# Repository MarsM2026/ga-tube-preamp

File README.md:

# Warm opamp preamp – tube character, designed by a genetic algorithm

A stereo hi-fi preamp built with opamps that imitates the warm distortion character
of a **12AX7 tube stage**. The component values were found by a **genetic
algorithm** that compared thousands of ngspice simulations against a simulated tube.
Includes the KiCad 10 schematic, two PCB designs (through-hole to solder yourself,
SMD to have it assembled by a PCB fab) and full documentation.

A project by **KyntoSoftware**.

| | |
|---|---|
| Gain | 10 dB |
| Frequency response | 20 Hz – 20 kHz ±0.11 dB |
| Distortion at 1 V rms | 0.31 % (almost only H2, the same as the 12AX7) |
| Signal-to-noise | approx. 97.5 dB re 1 V rms |
| Parts | 3× NE5532, 12× 1N4148, 1 % resistors, 2 trimmers |
| Power | ±15 V regulated |
| PCB | 2 layers; through-hole 178 × 100 mm or SMD 129 × 72 mm (assembled by a fab) |

**Status:** fully simulated and checked (NE5532 model, Monte Carlo tolerances,
ERC/DRC without errors). Not yet physically built and measured.

## Where to find what

| Folder / file | Content |
|---|---|
| [docs/](docs/README.md) | **documentation**: how it works, design process, results, build guide |
| `docs/img/`, `docs/data/` | charts and raw numbers (JSON/CSV) |
| `hardware/kicad/`, `hardware/export/` | through-hole: KiCad 10 project, Gerbers, schematic PDF/SVG, PCB layers, 3D renders, parts list |
| `hardware/kicad_smd/`, `hardware/export_smd/` | SMD version: same, plus assembly files for the fab ([explanation](docs/07_assembled_smd.md)) |
| `designs/` | design values per GA run and the final design (`final.json`) |
| `circuitbuilder/` | Python package: ngspice wrapper, analysis, candidate, fitness, as-built design |
| `scripts/` | every step: reference, GA, checks, schematic, PCB, documentation |

## Quick start

```powershell
python -m venv .venv
.\.venv\Scripts\pip install -r requirements.txt
.\.venv\Scripts\python scripts\verify_build.py      # simulate the as-built circuit
.\.venv\Scripts\python scripts\make_hardware.py     # KiCad schematic, PCB, Gerbers, renders
.\.venv\Scripts\python scripts\make_hardware.py --variant smd   # same for the SMD version
```

Requires ngspice 47 in `tools/Spice64`, KiCad 10, and Java + Freerouting 2.5 in
`tools/freerouting/`. See [docs/06_software.md](docs/06_software.md) for all steps.

## License

Copyright © 2026 KyntoSoftware. Each kind of work has the license that was made for it.
All three are permissive: you may use, modify, share and sell, also commercially, as
long as you credit KyntoSoftware.

| What | License | File |
|---|---|---|
| Software (`circuitbuilder/`, `scripts/`) | MIT | [LICENSE](LICENSE) |
| Hardware design (`hardware/`, `designs/`) | CERN-OHL-P v2 | [LICENSE-HARDWARE](LICENSE-HARDWARE) |
| Documentation, charts and images (`docs/`) | CC BY 4.0 | [LICENSE-DOCS](LICENSE-DOCS) |

Third-party simulation models keep their own terms: the NE5534 macromodel in
`circuitbuilder/models/ne5532.lib` (TI/MicroSim, via the
[KiCad-Spice-Library](https://github.com/kicad-spice-library/KiCad-Spice-Library)) and
the 12AX7 model in `circuitbuilder/models/12ax7.lib` (after Norman Koren).

The design is provided as is, without warranty; see the license files. Building it
involves a ±15 V supply; mains-powered supplies should only be built by people
experienced with mains voltage.

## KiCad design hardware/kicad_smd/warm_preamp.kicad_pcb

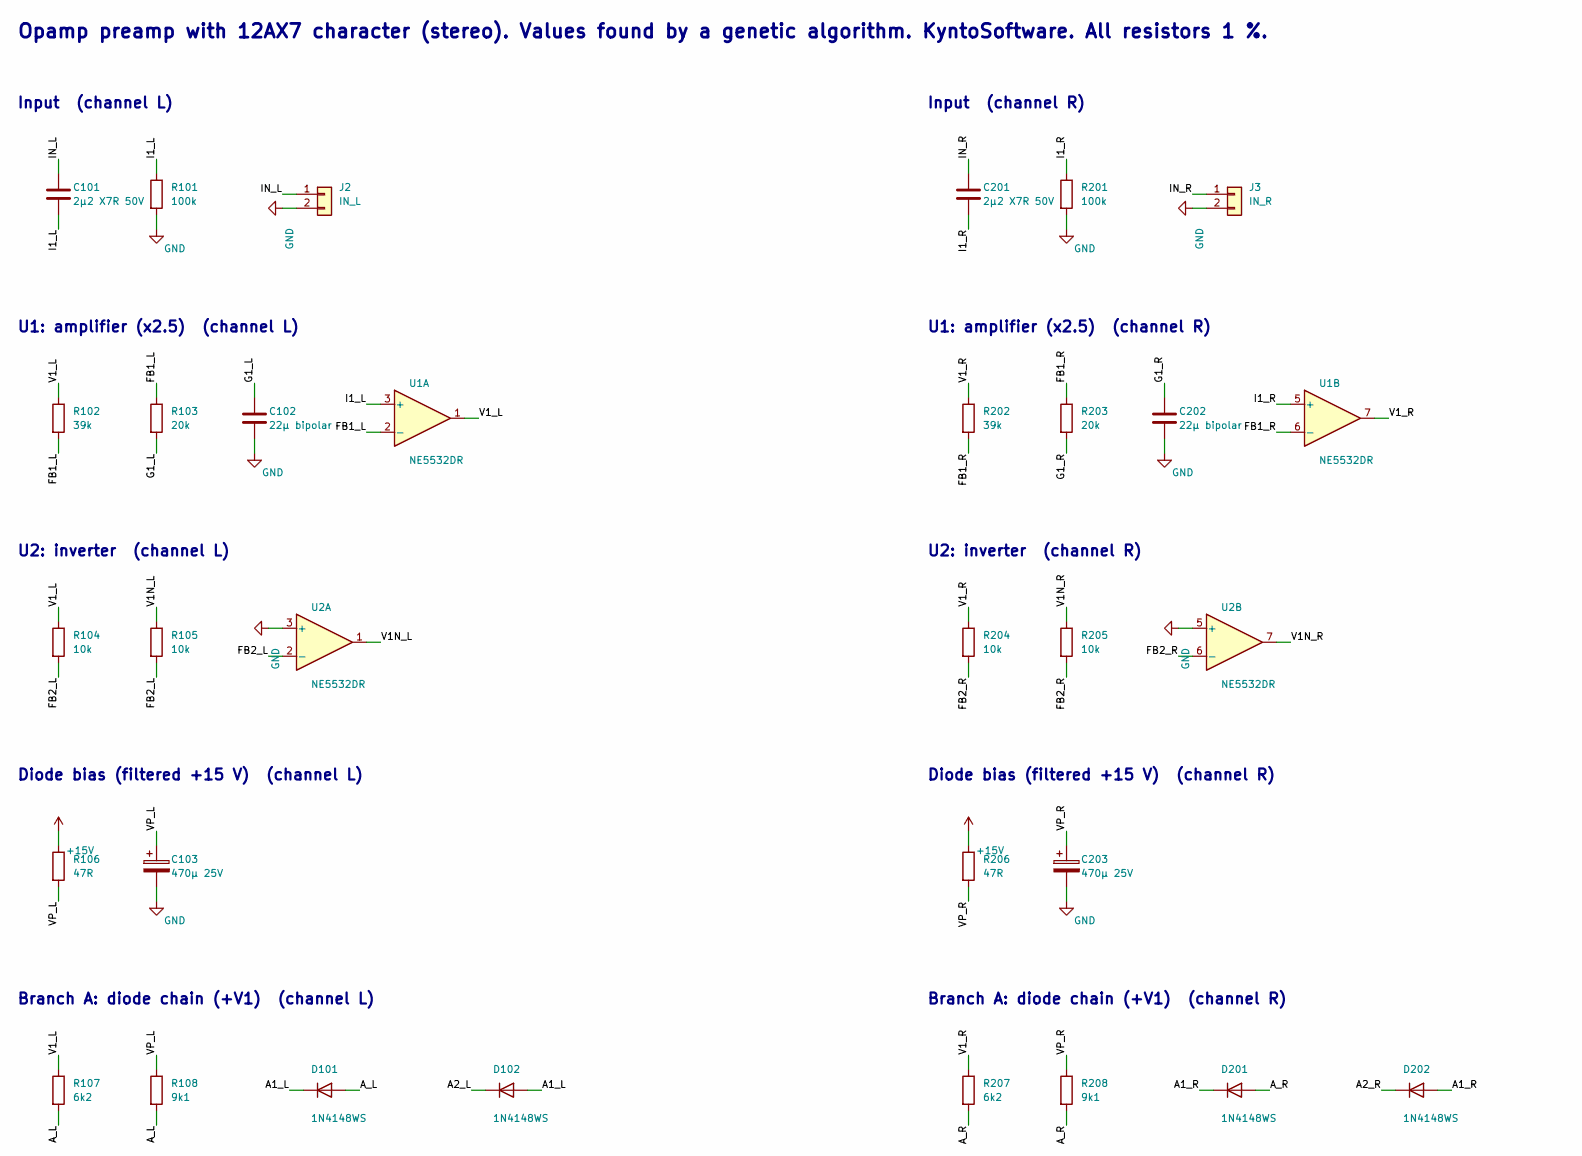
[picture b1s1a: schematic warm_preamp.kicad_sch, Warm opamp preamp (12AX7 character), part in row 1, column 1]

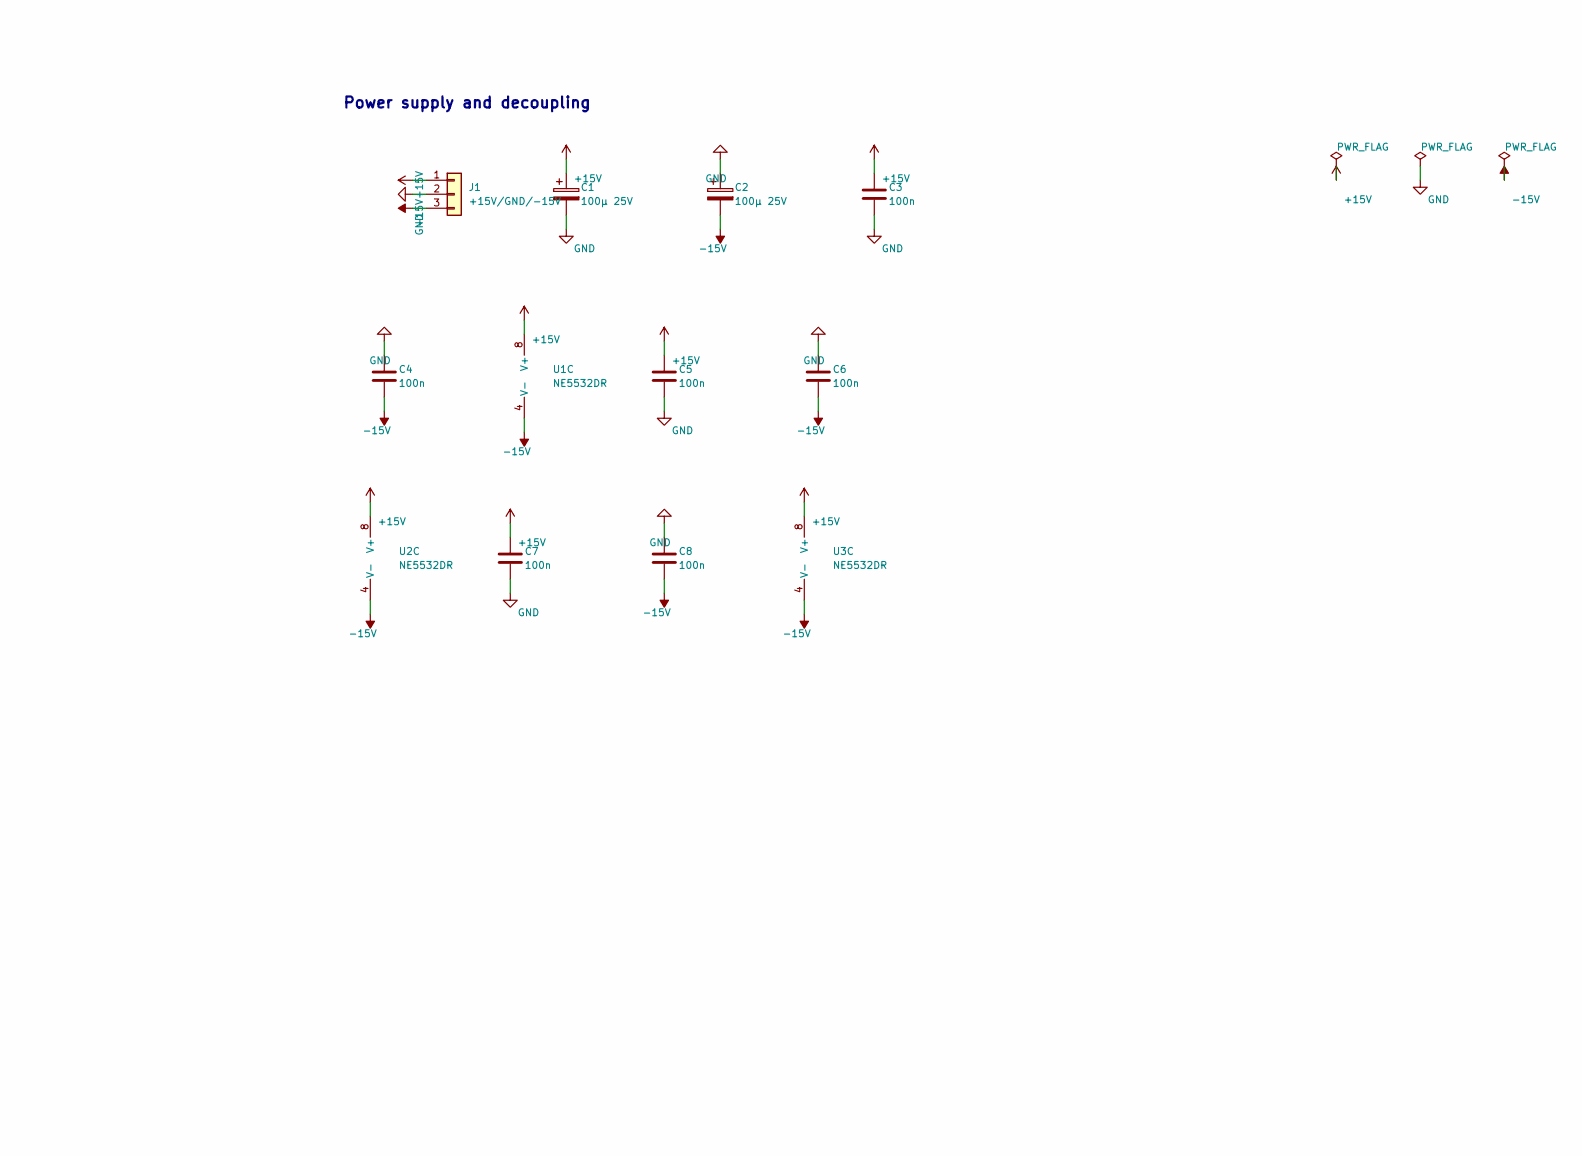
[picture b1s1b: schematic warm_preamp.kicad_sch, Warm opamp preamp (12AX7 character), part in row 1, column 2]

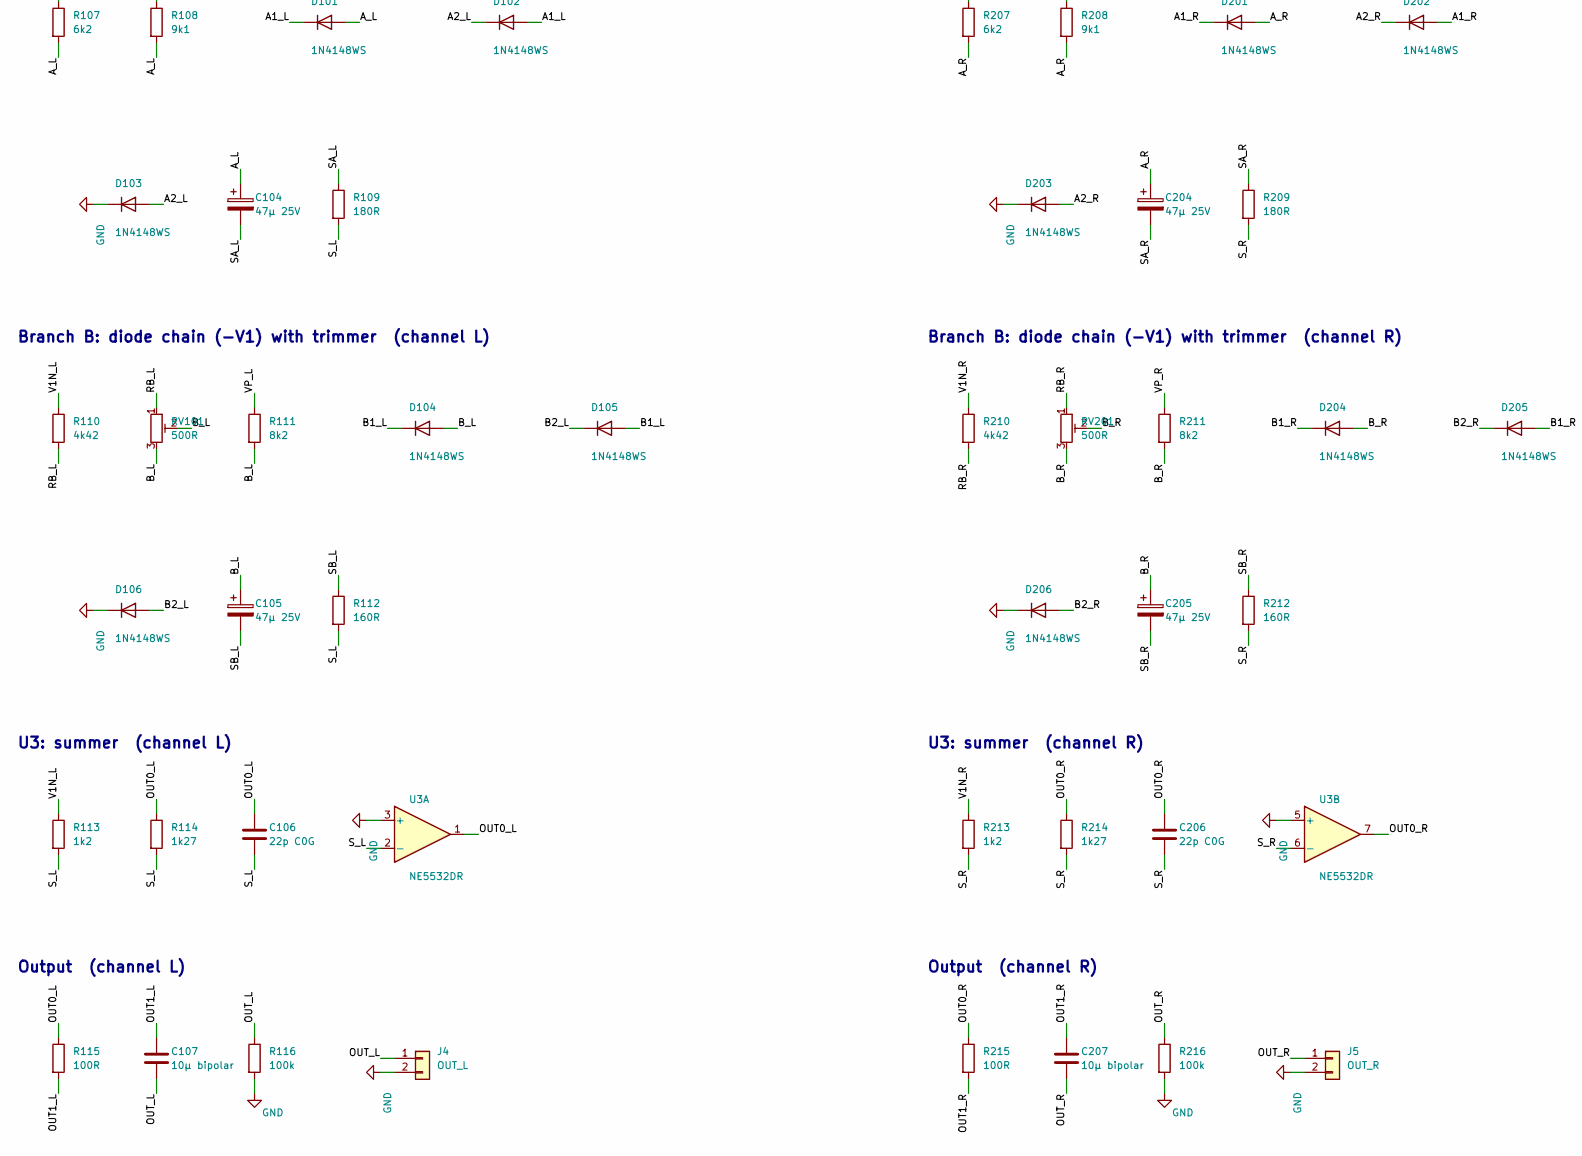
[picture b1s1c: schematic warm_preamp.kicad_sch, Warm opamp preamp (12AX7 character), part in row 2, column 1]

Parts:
C1, C2: 100µ 25V; CP_Elec_6.3x7.7
C3, C4, C5, C6, C7, C8: 100n; C_0805_2012Metric
C101, C201: 2µ2 X7R 50V; C_1206_3216Metric
C102, C202: 22µ bipolar; C_Elec_6.3x7.7
C103, C203: 470µ 25V; CP_Elec_10x10.5
C104, C105, C204, C205: 47µ 25V; CP_Elec_6.3x7.7
C106, C206: 22p C0G; C_0805_2012Metric
C107, C207: 10µ bipolar; C_Elec_6.3x7.7
D101, D102, D103, D104, D105, D106, D201, D202, D203, D204, D205, D206: 1N4148WS; D_SOD-323
J1: +15V/GND/-15V; TerminalBlock_Phoenix_MKDS-1,5-3-5.08_1x03_P5.08mm_Horizont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
J2: IN_L; TerminalBlock_Phoenix_MKDS-1,5-2-5.08_1x02_P5.08mm_Horizont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
J3: IN_R; TerminalBlock_Phoenix_MKDS-1,5-2-5.08_1x02_P5.08mm_Horizont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
J4: OUT_L; TerminalBlock_Phoenix_MKDS-1,5-2-5.08_1x02_P5.08mm_Horizont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
J5: OUT_R; TerminalBlock_Phoenix_MKDS-1,5-2-5.08_1x02_P5.08mm_Horizont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
R101, R116, R201, R216: 100k; R_0805_2012Metric
R102, R202: 39k; R_0805_2012Metric
R103, R203: 20k; R_0805_2012Metric
R104, R105, R204, R205: 10k; R_0805_2012Metric
R106, R206: 47R; R_0805_2012Metric
R107, R207: 6k2; R_0805_2012Metric
R108, R208: 9k1; R_0805_2012Metric
R109, R209: 180R; R_0805_2012Metric
R110, R210: 4k42; R_0805_2012Metric
R111, R211: 8k2; R_0805_2012Metric
R112, R212: 160R; R_0805_2012Metric
R113, R213: 1k2; R_0805_2012Metric
R114, R214: 1k27; R_0805_2012Metric
R115, R215: 100R; R_0805_2012Metric
RV101, RV201: 500R; Potentiometer_Bourns_3224W_Vertical
U1, U2, U3: NE5532DR; SOIC-8_3.9x4.9mm_P1.27mm

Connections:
+15V: C1.1, C3.1, C5.1, C7.1, J1.1, R106.1, R206.1, U1.8 (V+), U2.8 (V+), U3.8 (V+)
-15V: C2.2, C4.2, C6.2, C8.2, J1.3, U1.4 (V-), U2.4 (V-), U3.4 (V-)
/A1_L: D101.1 (K), D102.2 (A)
/A1_R: D201.1 (K), D202.2 (A)
/A2_L: D102.1 (K), D103.2 (A)
/A2_R: D202.1 (K), D203.2 (A)
/A_L: C104.1, D101.2 (A), R107.2, R108.2
/A_R: C204.1, D201.2 (A), R207.2, R208.2
/B1_L: D104.1 (K), D105.2 (A)
/B1_R: D204.1 (K), D205.2 (A)
/B2_L: D105.1 (K), D106.2 (A)
/B2_R: D205.1 (K), D206.2 (A)
/B_L: C105.1, D104.2 (A), R111.2, RV101.2, RV101.3
/B_R: C205.1, D204.2 (A), R211.2, RV201.2, RV201.3
/FB1_L: R102.2, R103.1, U1.2 (-)
/FB1_R: R202.2, R203.1, U1.6 (-)
/FB2_L: R104.2, R105.2, U2.2 (-)
/FB2_R: R204.2, R205.2, U2.6 (-)
/G1_L: C102.1, R103.2
/G1_R: C202.1, R203.2
/I1_L: C101.2, R101.1, U1.3 (+)
/I1_R: C201.2, R201.1, U1.5 (+)
/IN_L: C101.1, J2.1
/IN_R: C201.1, J3.1
/OUT0_L: C106.1, R114.1, R115.1, U3.1
/OUT0_R: C206.1, R214.1, R215.1, U3.7
/OUT1_L: C107.1, R115.2
/OUT1_R: C207.1, R215.2
/OUT_L: C107.2, J4.1, R116.1
/OUT_R: C207.2, J5.1, R216.1
/RB_L: R110.2, RV101.1
/RB_R: R210.2, RV201.1
/SA_L: C104.2, R109.1
/SA_R: C204.2, R209.1
/SB_L: C105.2, R112.1
/SB_R: C205.2, R212.1
/S_L: C106.2, R109.2, R112.2, R113.2, R114.2, U3.2 (-)
/S_R: C206.2, R209.2, R212.2, R213.2, R214.2, U3.6 (-)
/V1N_L: R105.1, R110.1, R113.1, U2.1
/V1N_R: R205.1, R210.1, R213.1, U2.7
/V1_L: R102.1, R104.1, R107.1, U1.1
/V1_R: R202.1, R204.1, R207.1, U1.7
/VP_L: C103.1, R106.2, R108.1, R111.1
/VP_R: C203.1, R206.2, R208.1, R211.1
GND: C1.2, C2.1, C3.2, C4.1, C5.2, C6.1, C7.2, C8.1, C102.2, C103.2, C202.2, C203.2, D103.1 (K), D106.1 (K), D203.1 (K), D206.1 (K), J1.2, J2.2, J3.2, J4.2, J5.2, R101.2, R116.2, R201.2, R216.2, U2.3 (+), U2.5 (+), U3.3 (+), U3.5 (+)

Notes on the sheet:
Input (channel L)
U1: amplifier (x2.5) (channel L)
U2: inverter (channel L)
Diode bias (filtered +15 V) (channel L)
Branch A: diode chain (+V1) (channel L)
Branch B: diode chain (-V1) with trimmer (channel L)
U3: summer (channel L)
Output (channel L)
Input (channel R)
U1: amplifier (x2.5) (channel R)
U2: inverter (channel R)
Diode bias (filtered +15 V) (channel R)
Branch A: diode chain (+V1) (channel R)
Branch B: diode chain (-V1) with trimmer (channel R)
U3: summer (channel R)
Output (channel R)
Power supply and decoupling
Opamp preamp with 12AX7 character (stereo). Values found by a genetic algorithm. KyntoSoftware. All resistors 1 %.

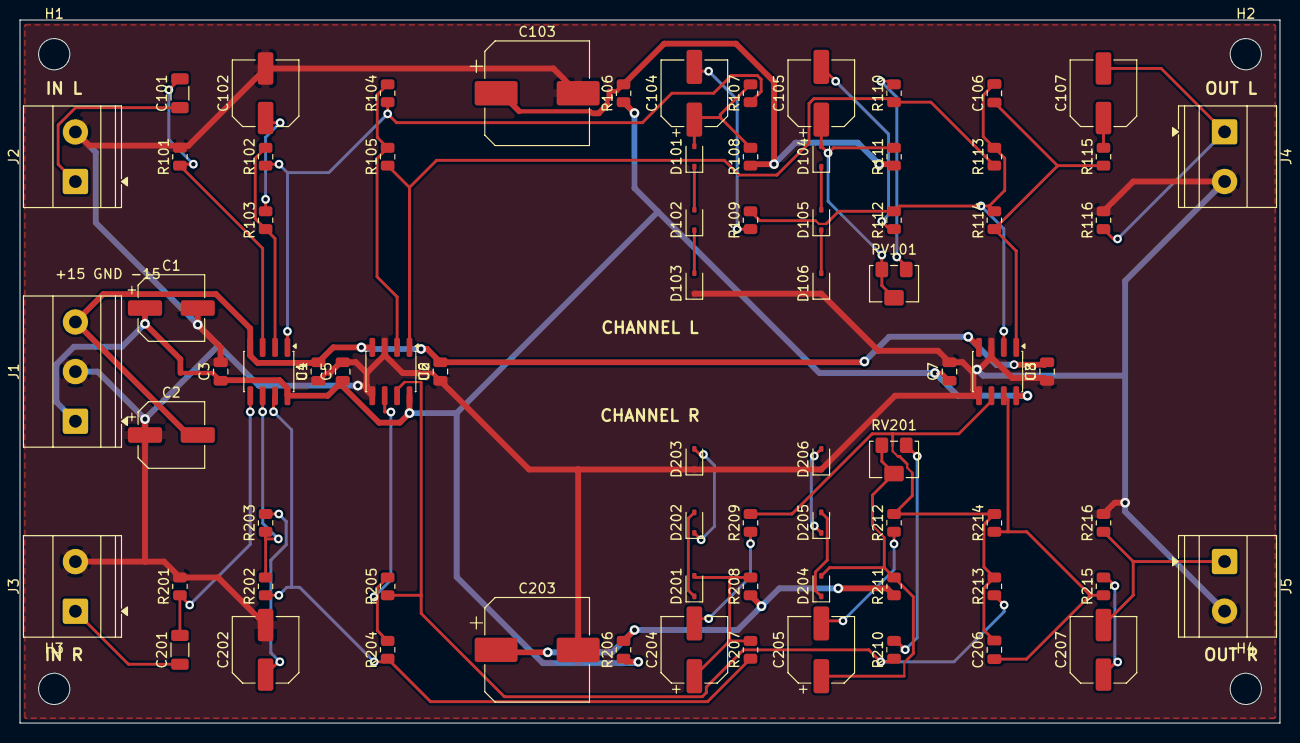
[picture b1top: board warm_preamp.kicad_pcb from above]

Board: 2 copper layers, 129.0 x 72.0 mm, 80 parts (0 on the bottom side), 45 nets.

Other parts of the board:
H1, H2, H3, H4: M3; MountingHole_3.2mm_M3

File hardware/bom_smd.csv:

qty;value;type;references;footprint
3;NE5532DR;Opamp NE5532 (SOIC-8);U1 U2 U3;Package_SO:SOIC-8_3.9x4.9mm_P1.27mm
12;1N4148WS;Diode SMD (SOD-323);D101 D102 D103 D104 D105 D106 D201 D202 D203 D204 D205 D206;Diode_SMD:D_SOD-323
2;100R;Resistor thick film 1% 0805;R115 R215;Resistor_SMD:R_0805_2012Metric
4;100k;Resistor thick film 1% 0805;R101 R116 R201 R216;Resistor_SMD:R_0805_2012Metric
4;10k;Resistor thick film 1% 0805;R104 R105 R204 R205;Resistor_SMD:R_0805_2012Metric
2;160R;Resistor thick film 1% 0805;R112 R212;Resistor_SMD:R_0805_2012Metric
2;180R;Resistor thick film 1% 0805;R109 R209;Resistor_SMD:R_0805_2012Metric
2;1k2;Resistor thick film 1% 0805;R113 R213;Resistor_SMD:R_0805_2012Metric
2;1k27;Resistor thick film 1% 0805;R114 R214;Resistor_SMD:R_0805_2012Metric
2;20k;Resistor thick film 1% 0805;R103 R203;Resistor_SMD:R_0805_2012Metric
2;39k;Resistor thick film 1% 0805;R102 R202;Resistor_SMD:R_0805_2012Metric
2;47R;Resistor thick film 1% 0805;R106 R206;Resistor_SMD:R_0805_2012Metric
2;4k42;Resistor thick film 1% 0805;R110 R210;Resistor_SMD:R_0805_2012Metric
2;6k2;Resistor thick film 1% 0805;R107 R207;Resistor_SMD:R_0805_2012Metric
2;8k2;Resistor thick film 1% 0805;R111 R211;Resistor_SMD:R_0805_2012Metric
2;9k1;Resistor thick film 1% 0805;R108 R208;Resistor_SMD:R_0805_2012Metric
2;500R;Trimmer multi-turn SMD (Bourns 3224W);RV101 RV201;Potentiometer_SMD:Potentiometer_Bourns_3224W_Vertical
6;100n;Capacitor SMD;C3 C4 C5 C6 C7 C8;Capacitor_SMD:C_0805_2012Metric
2;22p C0G;Capacitor SMD;C106 C206;Capacitor_SMD:C_0805_2012Metric
2;2µ2 X7R 50V;Capacitor SMD;C101 C201;Capacitor_SMD:C_1206_3216Metric
2;100µ 25V;Electrolytic SMD (polarised);C1 C2;Capacitor_SMD:CP_Elec_6.3x7.7
2;470µ 25V;Electrolytic SMD (polarised);C103 C203;Capacitor_SMD:CP_Elec_10x10.5
4;47µ 25V;Electrolytic SMD (polarised);C104 C105 C204 C205;Capacitor_SMD:CP_Elec_6.3x7.7
2;10µ bipolar;Electrolytic SMD bipolar (NP);C107 C207;Capacitor_SMD:C_Elec_6.3x7.7
2;22µ bipolar;Electrolytic SMD bipolar (NP);C102 C202;Capacitor_SMD:C_Elec_6.3x7.7
1;+15V/GND/-15V;Screw terminal 3-pin 5.08 mm (through-hole);J1;TerminalBlock_Phoenix:TerminalBlock_Phoenix_MKDS-1,5-3-5.08_1x03_P5.08mm_Horizontal
1;IN_L;Screw terminal 2-pin 5.08 mm (through-hole);J2;TerminalBlock_Phoenix:TerminalBlock_Phoenix_MKDS-1,5-2-5.08_1x02_P5.08mm_Horizontal
1;IN_R;Screw terminal 2-pin 5.08 mm (through-hole);J3;TerminalBlock_Phoenix:TerminalBlock_Phoenix_MKDS-1,5-2-5.08_1x02_P5.08mm_Horizontal
1;OUT_L;Screw terminal 2-pin 5.08 mm (through-hole);J4;TerminalBlock_Phoenix:TerminalBlock_Phoenix_MKDS-1,5-2-5.08_1x02_P5.08mm_Horizontal
1;OUT_R;Screw terminal 2-pin 5.08 mm (through-hole);J5;TerminalBlock_Phoenix:TerminalBlock_Phoenix_MKDS-1,5-2-5.08_1x02_P5.08mm_Horizontal
